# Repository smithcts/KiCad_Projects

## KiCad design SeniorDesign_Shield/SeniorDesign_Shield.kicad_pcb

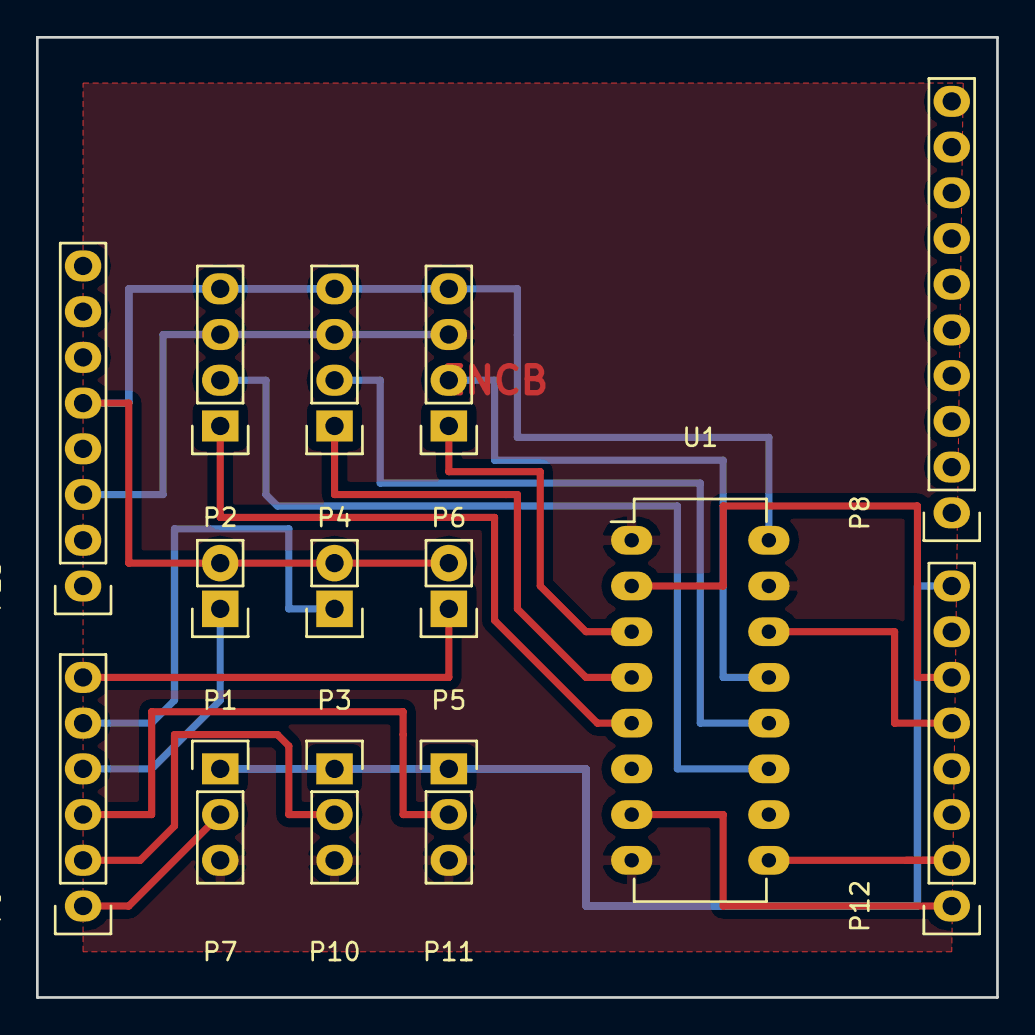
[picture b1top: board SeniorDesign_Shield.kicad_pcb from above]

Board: 2 copper layers, 53.3 x 53.3 mm, 14 parts (0 on the bottom side), 19 nets.

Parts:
P1: Motor1; Pin_Header_Straight_1x03
P2: ENC1; Pin_Header_Straight_1x04
P3: Motor2; Pin_Header_Straight_1x03
P4: ENC2; Pin_Header_Straight_1x04
P5: Motor3; Pin_Header_Straight_1x03
P6: ENC3; Pin_Header_Straight_1x04
P7: Limit1; Pin_Header_Straight_1x02
P8: Digital_10; Socket_Strip_Arduino_1x10
P9: Analog; Socket_Strip_Arduino_1x06
P10: Limit2; Pin_Header_Straight_1x02
P11: Limit3; Pin_Header_Straight_1x02
P12: Digital_8; Socket_Strip_Arduino_1x08
P13: Power; Socket_Strip_Arduino_1x08
U1: 74LS153; DIP-16_W7.62mm_LongPads

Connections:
+3V3: P2.4, P4.4, P6.4, P7.2, P10.2, P11.2, P13.5, U1.16
Enc_InputA: P12.1, U1.7
Enc_InputB: P12.2, U1.9
Encoder1A: P2.1, U1.5
Encoder1B: P2.2, U1.11
Encoder2A: P4.1, U1.4
Encoder2B: P4.2, U1.12
Encoder3A: P6.1, U1.3
Encoder3B: P6.2, U1.13
GND: P1.3, P2.3, P3.3, P4.3, P5.3, P6.3, P13.3, U1.1, U1.8, U1.15
Limit1: P7.1, P9.4
Limit2: P9.5, P10.1
Limit3: P9.6, P11.1
Motor1: P1.2, P9.1
Motor2: P3.2, P9.2
Motor3: P5.2, P9.3
MotorDir: P1.1, P3.1, P5.1, P12.8
SelectA: P12.5, U1.14
SelectB: P12.6, U1.2

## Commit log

2016-07-30 Added Senior Design Shield
2016-07-31 Added copper board png
